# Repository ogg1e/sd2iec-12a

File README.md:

# sd2iec-1.2a
SD2IEC v1.2a Schematics in Eagle Format

I modified the design to remove all the extra headers and add next/prev/reset buttons based on tactile switches from e-switch (4.5x4.5mm smd).
It also uses a connector from amp to connect to the serial port and cassette port for power. It's optional of course and you can just wire it directly to the board.

The sd card slot I used was like this one (26x26x2.5mm):

https://www.ebay.ca/sch/i.html?_odkw=pull+out+sd+card&_osacat=0&_from=R40&_trksid=p2045573.m570.l1313.TR0.TRC0.H0.X26+pull+out+sd+card.TRS1&_nkw=26+pull+out+sd+card&_sacat=0

I also added a BOM that can be used at digikey. All parts where in stock when I created the BOM.

Based on the work from here: https://www.c64-wiki.com/wiki/SD2IEC

direct Link: https://www.c64-wiki.com/images/0/0d/sd2iec_12a_full.zip

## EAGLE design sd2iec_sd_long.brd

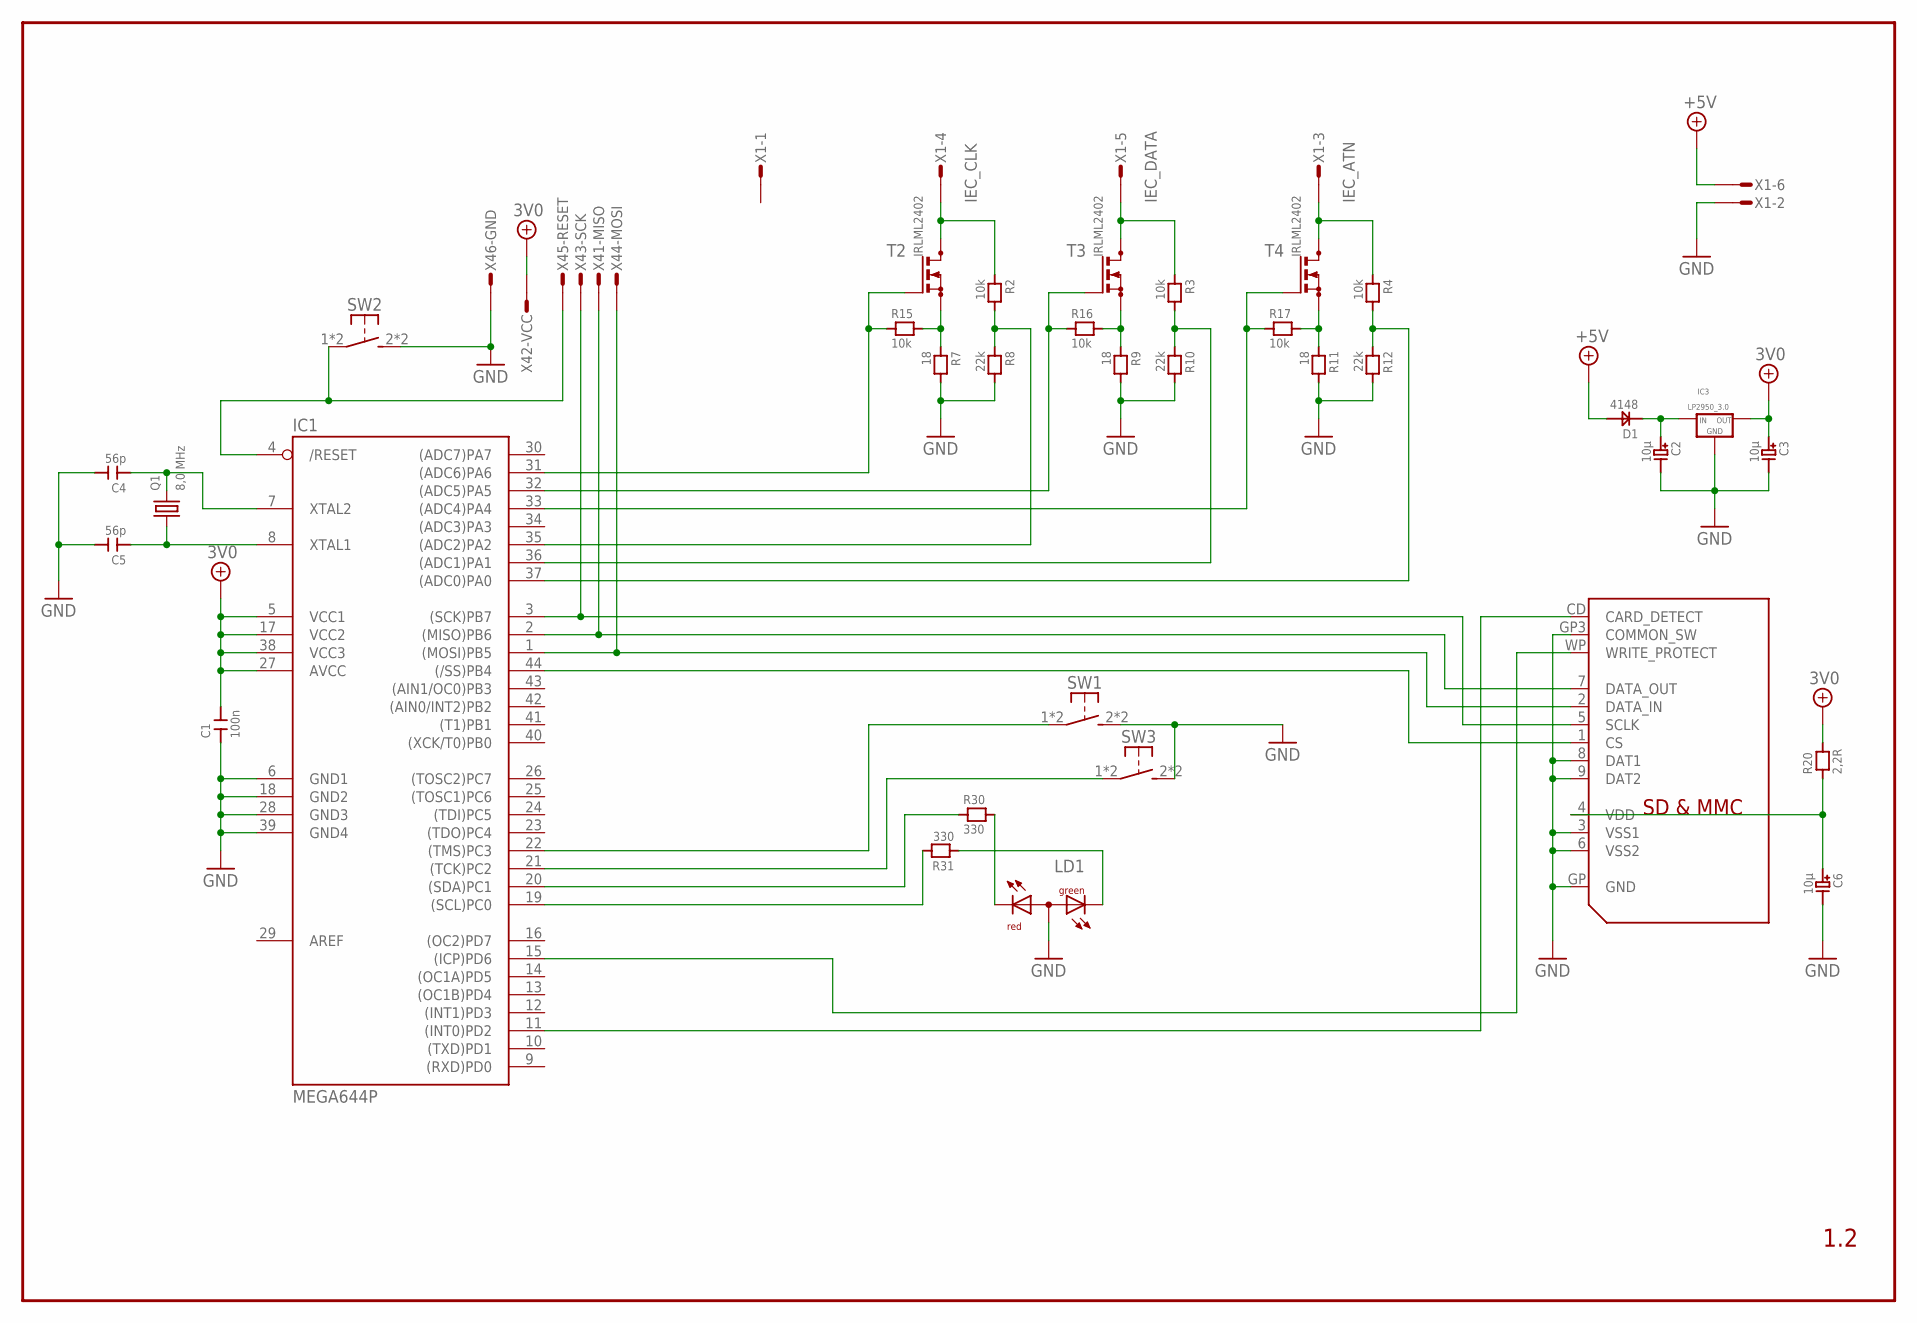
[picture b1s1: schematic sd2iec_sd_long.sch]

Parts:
C1: 100n; C1206
C2, C3, C6: 10µ; C_TANTAL_A
C4, C5: 56p; C1206
D1: 4148; SOD-123
IC1: MEGA644P; TQFP44
IC3: LP2950_3.0; TO92_S
LD1: DUOLED-RG-A; DUOLED-A-5MM
Q1: 8,0 MHz; HC49/S
R2, R3, R4: 10k; R1206
R7, R9, R11: 18; R1206
R8, R10, R12: 22k; R1206
R15, R16, R17: 10k; R0805
R20: 2,2R; R1206
R30, R31: 330; R1206
SW1: Disk Next; TL3305
SW2: Reset; TL3305
SW3: Disk Prev; TL3305
T2, T3, T4: IRLML2402; SOT23_C
U$6: SDMMC06132; 06132
X1: MICROMATCH-6_PIN; MICROMATCH-6
X4: AVR-ISP_1X6; 1X6_ISP

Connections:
3V0: C1.2, C3.1, IC1.5 (VCC1), IC1.17 (VCC2), IC1.27 (AVCC), IC1.38 (VCC3), IC3.3 (OUT), R20.2, X4.2
+5V: D1.2, X1.6
/RESET: IC1.4 (/RESET), SW2.1, SW2.4 (P1), X4.5
ATN: IC1.37 ((ADC0)PA0), R4.2, R12.1
CD: IC1.11 ((INT0)PD2), U$6.CD (CARD_DETECT)
CLK: IC1.35 ((ADC2)PA2), R2.2, R8.1
CS: IC1.44 ((/SS)PB4), U$6.1 (CS)
DATA: IC1.36 ((ADC1)PA1), R3.2, R10.1
DISKNEXT: IC1.22 ((TMS)PC3), SW1.1, SW1.4 (P1)
DISKPREV: IC1.21 ((TCK)PC2), SW3.1, SW3.4 (P1)
GND: C1.1, C2.2, C3.2, C4.2, C5.2, C6.2, IC1.6 (GND1), IC1.18 (GND2), IC1.28 (GND3), IC1.39 (GND4), IC3.2 (GND), LD1.A, R7.2, R8.2, R9.2, R10.2, R11.2, R12.2, SW1.2 (S1), SW1.3 (S1), SW2.2 (S1), SW2.3 (S1), SW3.2 (S1), SW3.3 (S1), U$6.3 (VSS1), U$6.6 (VSS2), U$6.8 (DAT1), U$6.9 (DAT2), U$6.GP (GND), U$6.GP3 (COMMON_SW), X1.2, X4.6
IEC_ATN: R4.1, T4.3 (D), X1.3
IEC_CLK: R2.1, T2.3 (D), X1.4
IEC_DATA: R3.1, T3.3 (D), X1.5
LED1: LD1.CR, R30.2
LED2: LD1.CX (CG), R31.1
MISO: IC1.2 ((MISO)PB6), U$6.7 (DATA_OUT), X4.1
MOSI: IC1.1 ((MOSI)PB5), U$6.2 (DATA_IN), X4.4
unnamed: C2.1, D1.1, IC3.1 (IN)
unnamed: C5.1, IC1.8 (XTAL1), Q1.1
unnamed: C4.1, IC1.7 (XTAL2), Q1.2
unnamed: IC1.32 ((ADC5)PA5), R16.1, T3.1 (G)
unnamed: IC1.33 ((ADC4)PA4), R17.1, T4.1 (G)
unnamed: IC1.31 ((ADC6)PA6), R15.1, T2.1 (G)
unnamed: R7.1, R15.2, T2.2 (S)
unnamed: R9.1, R16.2, T3.2 (S)
unnamed: R11.1, R17.2, T4.2 (S)
PC0: IC1.19 ((SCL)PC0), R31.2
PC1: IC1.20 ((SDA)PC1), R30.1
SCK: IC1.3 ((SCK)PB7), U$6.5 (SCLK), X4.3
VDD: C6.1, R20.1, U$6.4 (VDD)
WP: IC1.15 ((ICP)PD6), U$6.WP (WRITE_PROTECT)

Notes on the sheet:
1.2

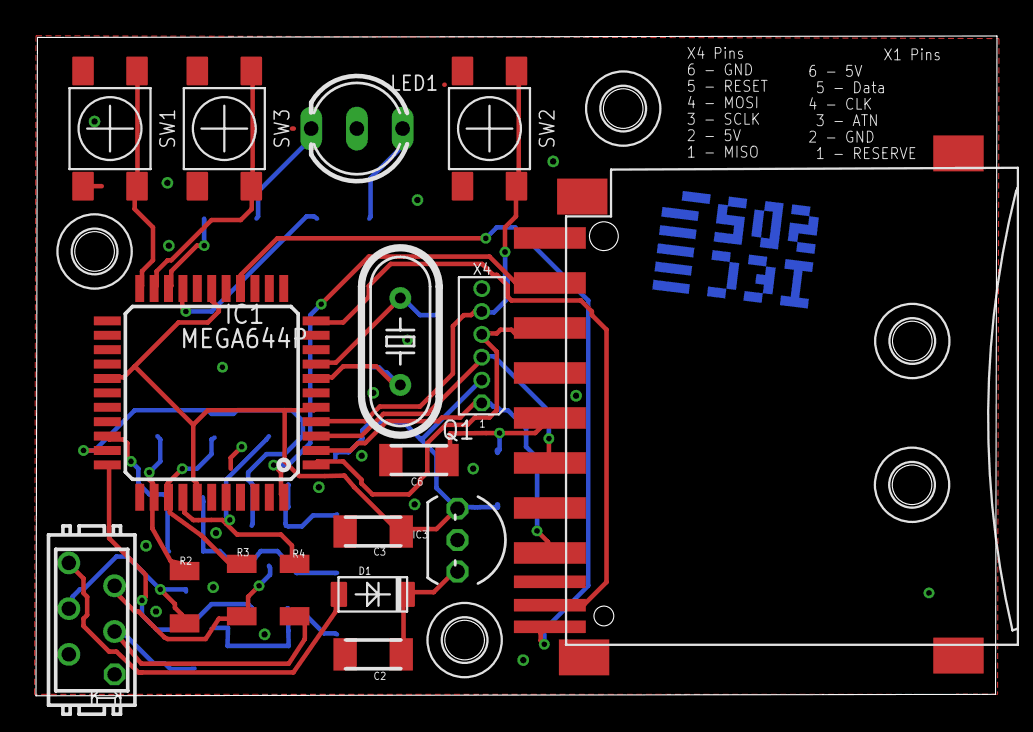
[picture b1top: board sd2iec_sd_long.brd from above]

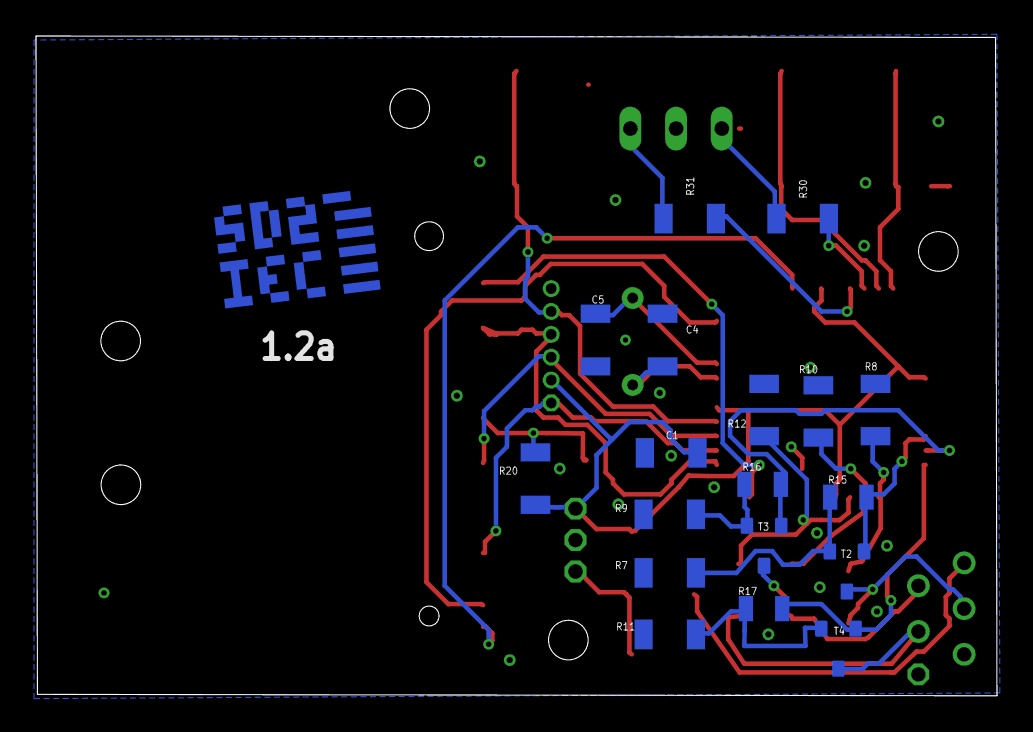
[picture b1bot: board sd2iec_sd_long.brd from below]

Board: 2 copper layers, 53.4 x 36.7 mm, 41 parts (19 on the bottom side), 32 nets.

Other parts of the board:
U$1, U$2, U$3, U$4, U$7: 2,2
U$5: SD2IEC_LOGO
